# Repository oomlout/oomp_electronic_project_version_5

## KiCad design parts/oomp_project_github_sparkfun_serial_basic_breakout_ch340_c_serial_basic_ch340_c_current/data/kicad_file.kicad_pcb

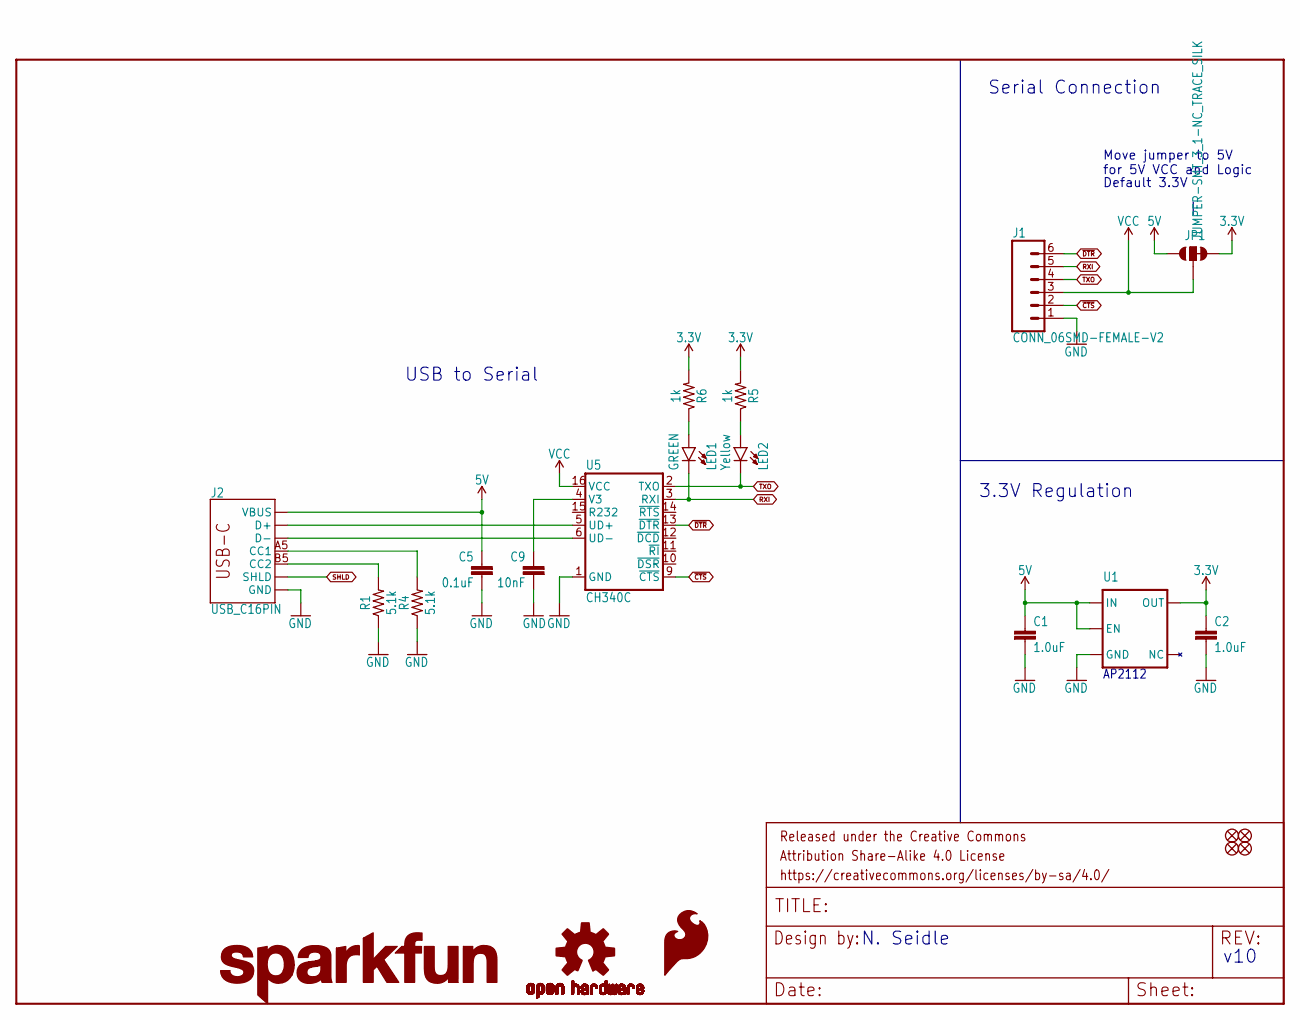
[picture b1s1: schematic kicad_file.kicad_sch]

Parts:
C1, C2: 1.0uF; 0603
C5: 0.1uF; 0603
C9: 10nF; 0603
FRAME1: FRAME-LETTER; CREATIVE_COMMONS
J1: CONN_06SMD-FEMALE-V2; 1X06-SMD-FEMALE
J2: USB_C16PIN; USB-C-16P
JP1: JUMPER-SMT_3_1-NC_TRACE_SILK; SMT-JUMPER_3_1-NC_TRACE_SILK
JP3, JP4, JP5, JP6: FIDUCIAL1X2; FIDUCIAL-1X2
LED1: GREEN; LED-0603
LED2: Yellow; LED-0603
LOGO1: OSHW-LOGOS; OSHW-LOGO-S
LOGO2: SFE_LOGO_FLAME.1_INCH; SFE_LOGO_FLAME_.1
LOGO3: SFE_LOGO_NAME.1_INCH; SFE_LOGO_NAME_.1
R1, R4: 5.1k; 0603
R5, R6: 1k; 0603
U1: 3.3V; SOT23-5
U5: CH340C; SO016

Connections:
3.3V: C2.1, JP1.3, R5.2, R6.2, U1.5 (OUT)
5V: C1.1, C5.1, J2.VBUS1 (VBUS), J2.VBUS2 (VBUS), JP1.1, U1.1 (IN), U1.3 (EN)
CC1: J2.A5 (CC1), R4.2
CC2: J2.B5 (CC2), R1.2
D+: J2.A6 (D+), J2.B6 (D+), U5.5 (UD+)
D-: J2.A7 (D-), J2.B7 (D-), U5.6 (UD-)
GND: C1.2, C2.2, C5.2, C9.2, J1.1, J2.GND, J2.GND2 (GND), R1.1, R4.1, U1.2 (GND), U5.1 (GND)
unnamed: C9.1, U5.4 (V3)
unnamed: LED1.A, R6.1
unnamed: LED2.A, R5.1
RXI: J1.5, LED1.C, U5.3 (RXI)
SHLD: J2.SHLD1 (SHLD), J2.SHLD2 (SHLD), J2.SHLD3 (SHLD), J2.SHLD4 (SHLD), J2.SHLD5 (SHLD), J2.SHLD6 (SHLD), J2.SHLD7 (SHLD), J2.SHLD8 (SHLD)
TXO: J1.4, LED2.C, U5.2 (TXO)
VCC: J1.3, JP1.2, U5.16 (VCC)
~CTS: J1.2, U5.9 (~CTS)
~DTR: J1.6, U5.13 (~DTR)

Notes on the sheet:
3.3V Regulation
v10
Default 3.3V
AP2112
USB to Serial
Serial Connection
N. Seidle
Move jumper to 5V for 5V VCC and Logic

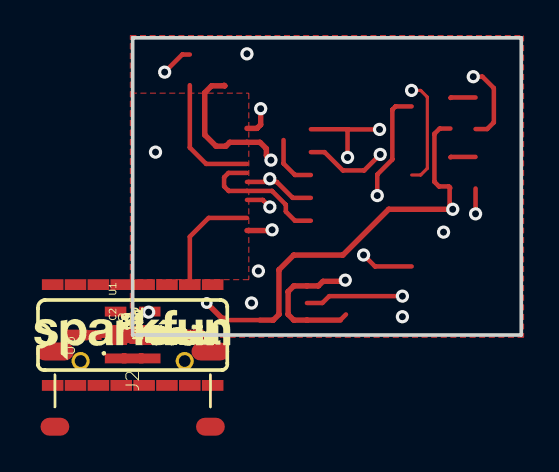
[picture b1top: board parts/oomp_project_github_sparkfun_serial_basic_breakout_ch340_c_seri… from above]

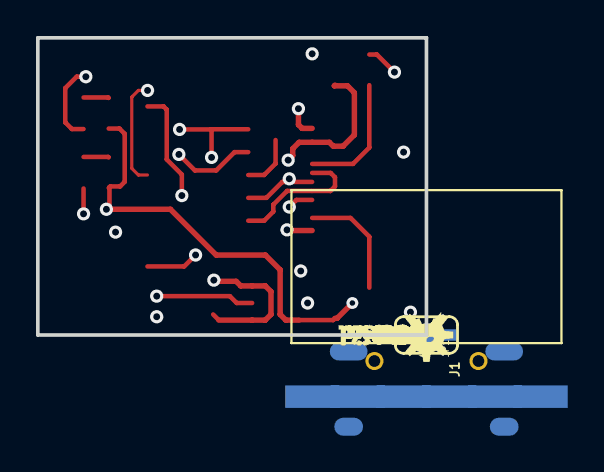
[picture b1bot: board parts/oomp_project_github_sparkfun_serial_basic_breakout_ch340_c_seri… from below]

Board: 4 copper layers, 21.6 x 16.5 mm, 43 parts (16 on the bottom side), 16 nets.

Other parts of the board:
U$1, U$14: CTS1
U$2: 3#3V8
U$3: 5V9
U$4, U$9: SERIAL0
U$5, U$12: TXO0
U$6, U$13: VCC2
U$7, U$11: BASIC1
U$8, U$18: DTR0
U$10, U$21: RXI1
U$15, U$19: GND5
U$17: BLK6
U$20: GRN7

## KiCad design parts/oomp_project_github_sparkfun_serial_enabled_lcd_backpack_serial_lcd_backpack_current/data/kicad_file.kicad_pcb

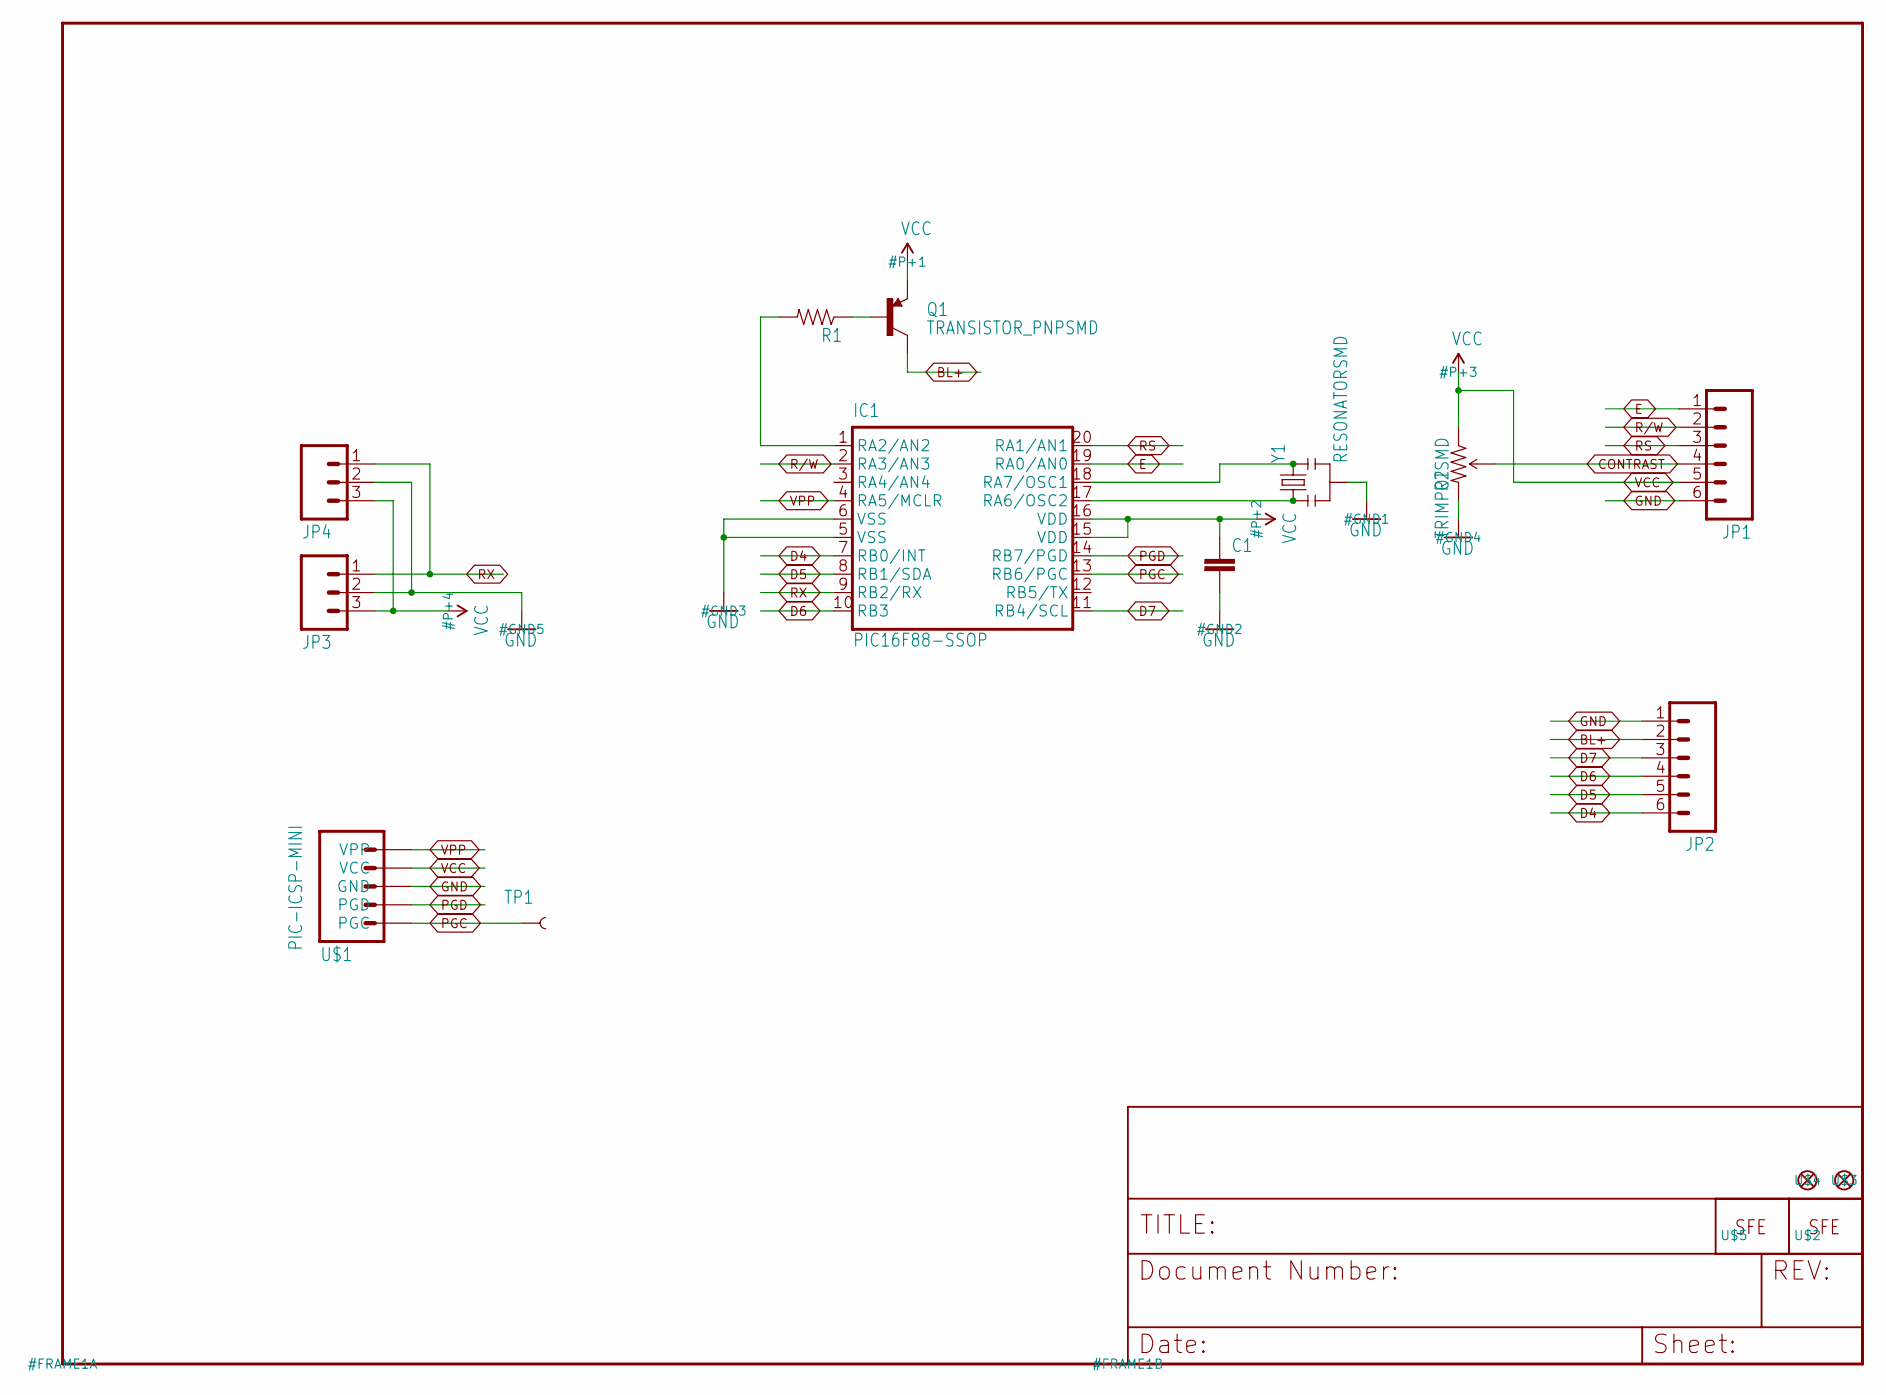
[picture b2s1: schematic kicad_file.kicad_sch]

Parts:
C1: CAP0402-CAP; 0402-CAP
IC1: PIC16F88-SSOP; SSOP20
JP1, JP2: M06LOCK; 1X06_LOCK
JP3: M03PTH; 1X03
JP4: M03SCREW_LOCK; SCREWTERMINAL-3.5MM-3_LOCK.007S
Q1: TRANSISTOR_PNPSMD; SOT23-3
R1: RESISTOR0402-RES; 0402-RES
R2: TRIMPOTSMD; TRIMPOT-3MM
TP1: TEST-POINT3X5; PAD.03X.05
U$1: PIC-ICSP-MINI
U$2: LOGO-FLAME-LARGE
U$3, U$4: FIDUCIAL1X2; FIDUCIAL-1X2
U$5: LOGO-SFENEW; SFE-NEW-WEBLOGO
Y1: RESONATORSMD; RESONATOR-SMD

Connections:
BL+: JP2.2, Q1.3 (C)
CONTRAST: JP1.4, R2.2 (WIPER)
D4: IC1.7 (RB0/INT), JP2.6
D5: IC1.8 (RB1/SDA), JP2.5
D6: IC1.10 (RB3), JP2.4
D7: IC1.11 (RB4/SCL), JP2.3
E: IC1.19 (RA0/AN0), JP1.1
GND: C1.2, IC1.5 (VSS), IC1.6 (VSS), JP1.6, JP2.1, JP3.2, JP4.2, R2.3 (CW), U$1.3 (GND), Y1.2
unnamed: IC1.18 (RA7/OSC1), Y1.3
unnamed: IC1.17 (RA6/OSC2), Y1.1
unnamed: IC1.1 (RA2/AN2), R1.2
unnamed: Q1.1 (B), R1.1
PGC: IC1.13 (RB6/PGC), TP1.P$1, U$1.5 (PGC)
PGD: IC1.14 (RB7/PGD), U$1.4 (PGD)
R/W: IC1.2 (RA3/AN3), JP1.2
RS: IC1.20 (RA1/AN1), JP1.3
RX: IC1.9 (RB2/RX), JP3.1, JP4.1
VCC: C1.1, IC1.15 (VDD), IC1.16 (VDD), JP1.5, JP3.3, JP4.3, Q1.2 (E), R2.1 (CCW), U$1.2 (VCC)
VPP: IC1.4 (RA5/MCLR), U$1.1 (VPP)

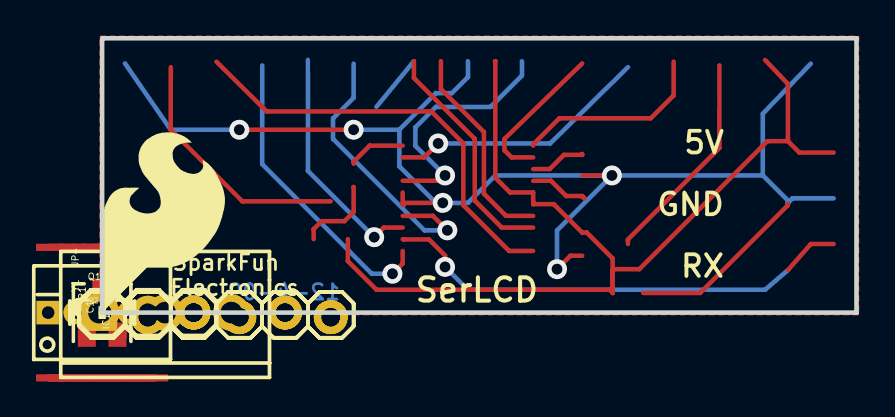
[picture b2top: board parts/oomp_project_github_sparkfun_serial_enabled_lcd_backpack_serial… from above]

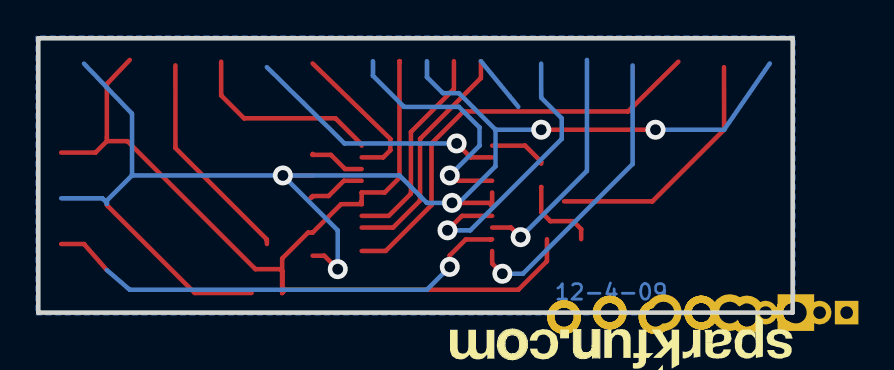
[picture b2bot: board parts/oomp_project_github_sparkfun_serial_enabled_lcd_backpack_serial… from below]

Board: 2 copper layers, 41.9 x 15.2 mm, 16 parts (2 on the bottom side), 19 nets.

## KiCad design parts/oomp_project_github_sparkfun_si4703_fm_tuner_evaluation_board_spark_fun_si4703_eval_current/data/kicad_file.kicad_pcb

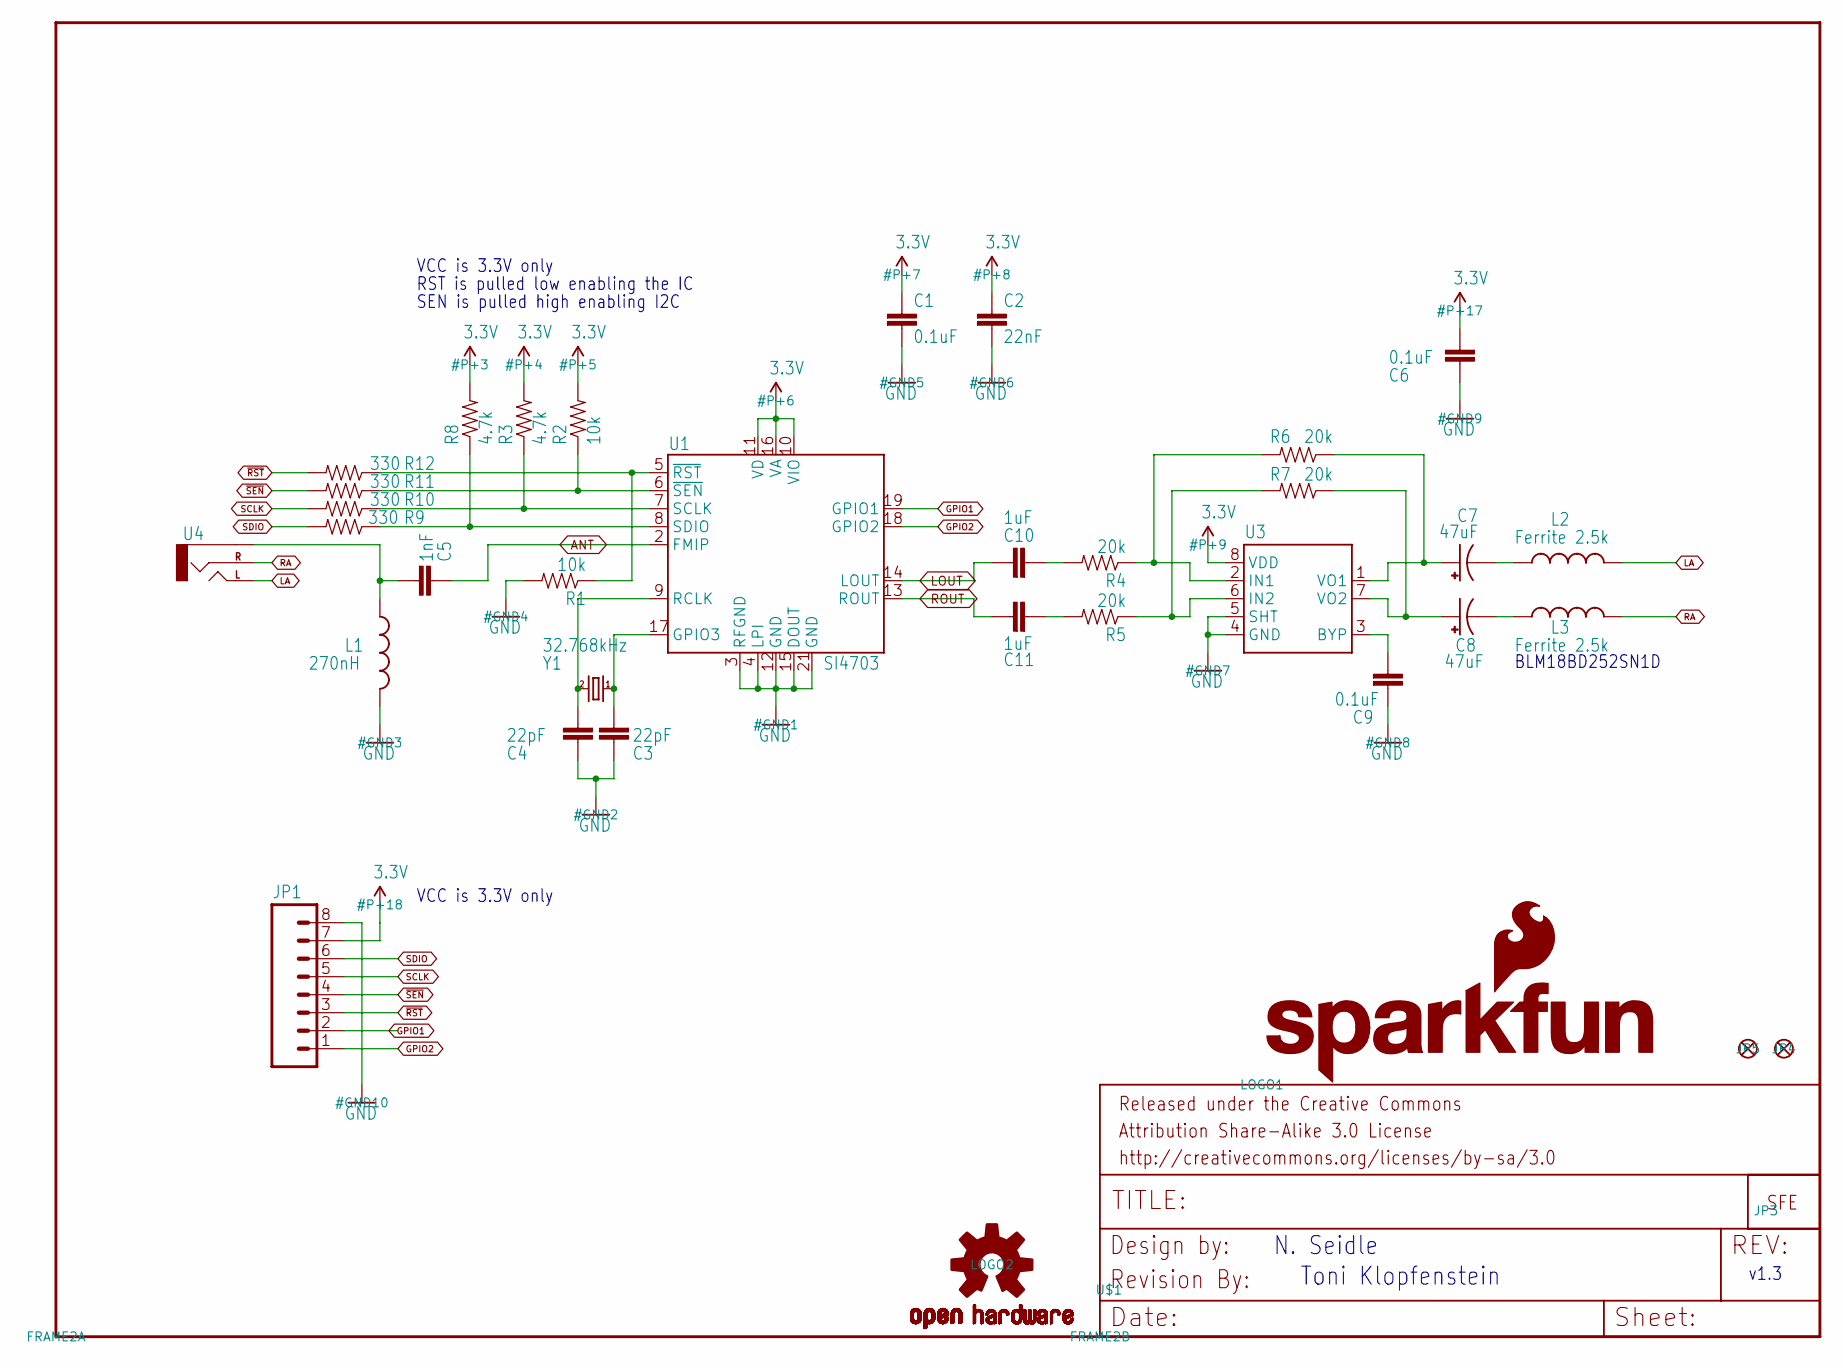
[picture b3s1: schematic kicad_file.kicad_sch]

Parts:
C1, C6, C9: 0.1uF; 0603-CAP
C2: 22nF; 0603-CAP
C3, C4: 22pF; 0603-CAP
C5: 1nF; 0603-CAP
C7, C8: 47uF; EIA3528
C10, C11: 1uF; 0603-CAP
FRAME2: FRAME-LETTER; CREATIVE_COMMONS
JP1: M08; 1X08
JP3: LOGO-SFESK; SFE-LOGO-FLAME
JP4, JP5: FIDUCIAL1X2; FIDUCIAL-1X2
L1: 270nH; 0603
L2, L3: Ferrite 2.5k; 0603
LOGO1: SFE_LOGO_NAME_FLAME.1_INCH; SFE_LOGO_NAME_FLAME_.1
LOGO2: OSHW-LOGOS; OSHW-LOGO-S
R1, R2: 10k; 0603-RES
R3, R8: 4.7k; 0603
R4, R5, R6, R7: 20k; 0603-RES
R9, R10, R11, R12: 330; 0603-RES
U1: SI4703; SI470X
U3: TPA6111; SO08-TIGHT
U4: AUDIO-JACKSMD2; AUDIO-JACK-3.5MM-SMD
U$1: REVISION
Y1: 32.768kHz; CRYSTAL-32KHZ-SMD

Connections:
3.3V: C1.1, C2.1, C6.2, JP1.7, R2.2, R3.2, R8.2, U1.10 (VIO), U1.11 (VD), U1.16 (VA), U3.8 (VDD)
ANT: C5.1, U1.2 (FMIP)
GND: C1.2, C2.2, C3.1, C4.1, C6.1, C9.2, JP1.8, L1.2, R1.2, U1.3 (RFGND), U1.4 (LPI), U1.12 (GND), U1.15 (DOUT), U1.21 (GND), U3.4 (GND), U3.5 (SHT)
GPIO1: JP1.2, U1.19 (GPIO1)
GPIO2: JP1.1, U1.18 (GPIO2)
LA: L2.2, U4.TIP (LEFT)
LOUT: C10.1, U1.14 (LOUT)
unnamed: C4.2, U1.9 (RCLK), Y1.X2 (2)
unnamed: C3.2, U1.17 (GPIO3), Y1.X1 (1)
unnamed: C5.2, L1.1, U4.SLEEVE
unnamed: C7.C (-), L2.1
unnamed: C7.A (+), R6.1, U3.1 (VO1)
unnamed: C8.A (+), R7.1, U3.7 (VO2)
unnamed: C8.C (-), L3.1
unnamed: C9.1, U3.3 (BYP)
unnamed: R4.1, R6.2, U3.2 (IN1)
unnamed: R5.1, R7.2, U3.6 (IN2)
unnamed: C10.2, R4.2
unnamed: C11.2, R5.2
RA: L3.2, U4.RING (RIGHT)
ROUT: C11.1, U1.13 (ROUT)
SCLK: JP1.5, R10.2
SCLK-L: R3.1, R10.1, U1.7 (SCLK)
SDIO: JP1.6, R9.2
SDIO-L: R8.1, R9.1, U1.8 (SDIO)
~RST-L: R1.1, R12.1, U1.5 (~RST)
~RST: JP1.3, R12.2
~SEN-L: R2.1, R11.1, U1.6 (~SEN)
~SEN: JP1.4, R11.2

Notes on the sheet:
VCC is 3.3V only~{}
N. Seidle
Toni Klopfenstein
SEN is pulled high enabling I2C
v1.3
BLM18BD252SN1D
RST is pulled low enabling the IC

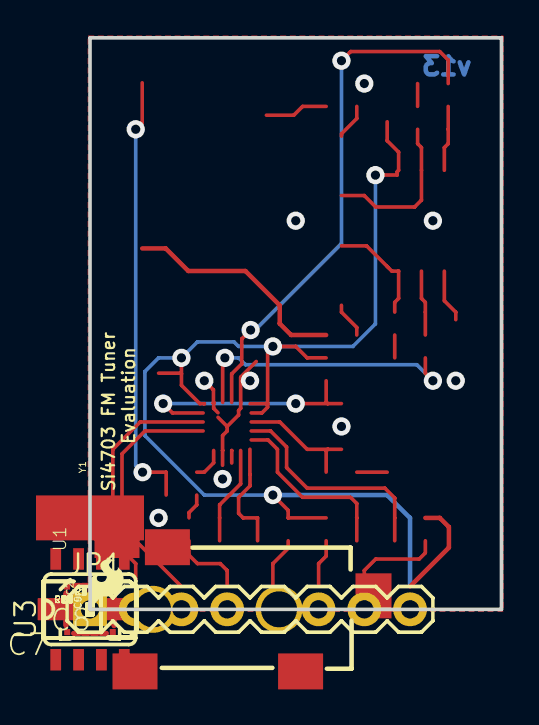
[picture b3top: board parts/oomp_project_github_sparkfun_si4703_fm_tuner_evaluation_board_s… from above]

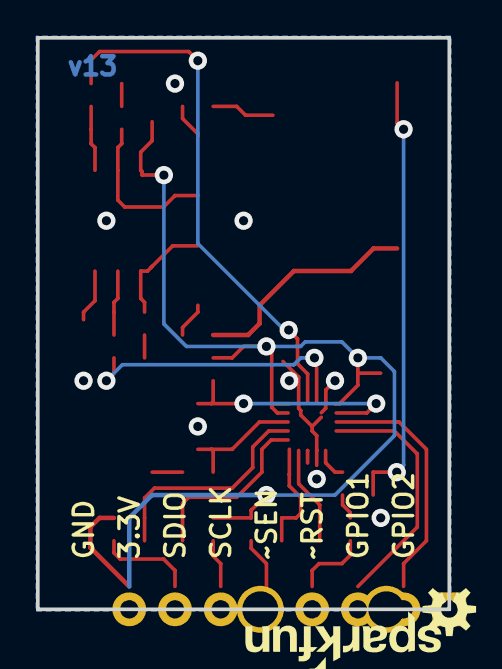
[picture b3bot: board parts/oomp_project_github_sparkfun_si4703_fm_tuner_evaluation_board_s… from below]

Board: 2 copper layers, 22.9 x 31.8 mm, 38 parts (2 on the bottom side), 29 nets.

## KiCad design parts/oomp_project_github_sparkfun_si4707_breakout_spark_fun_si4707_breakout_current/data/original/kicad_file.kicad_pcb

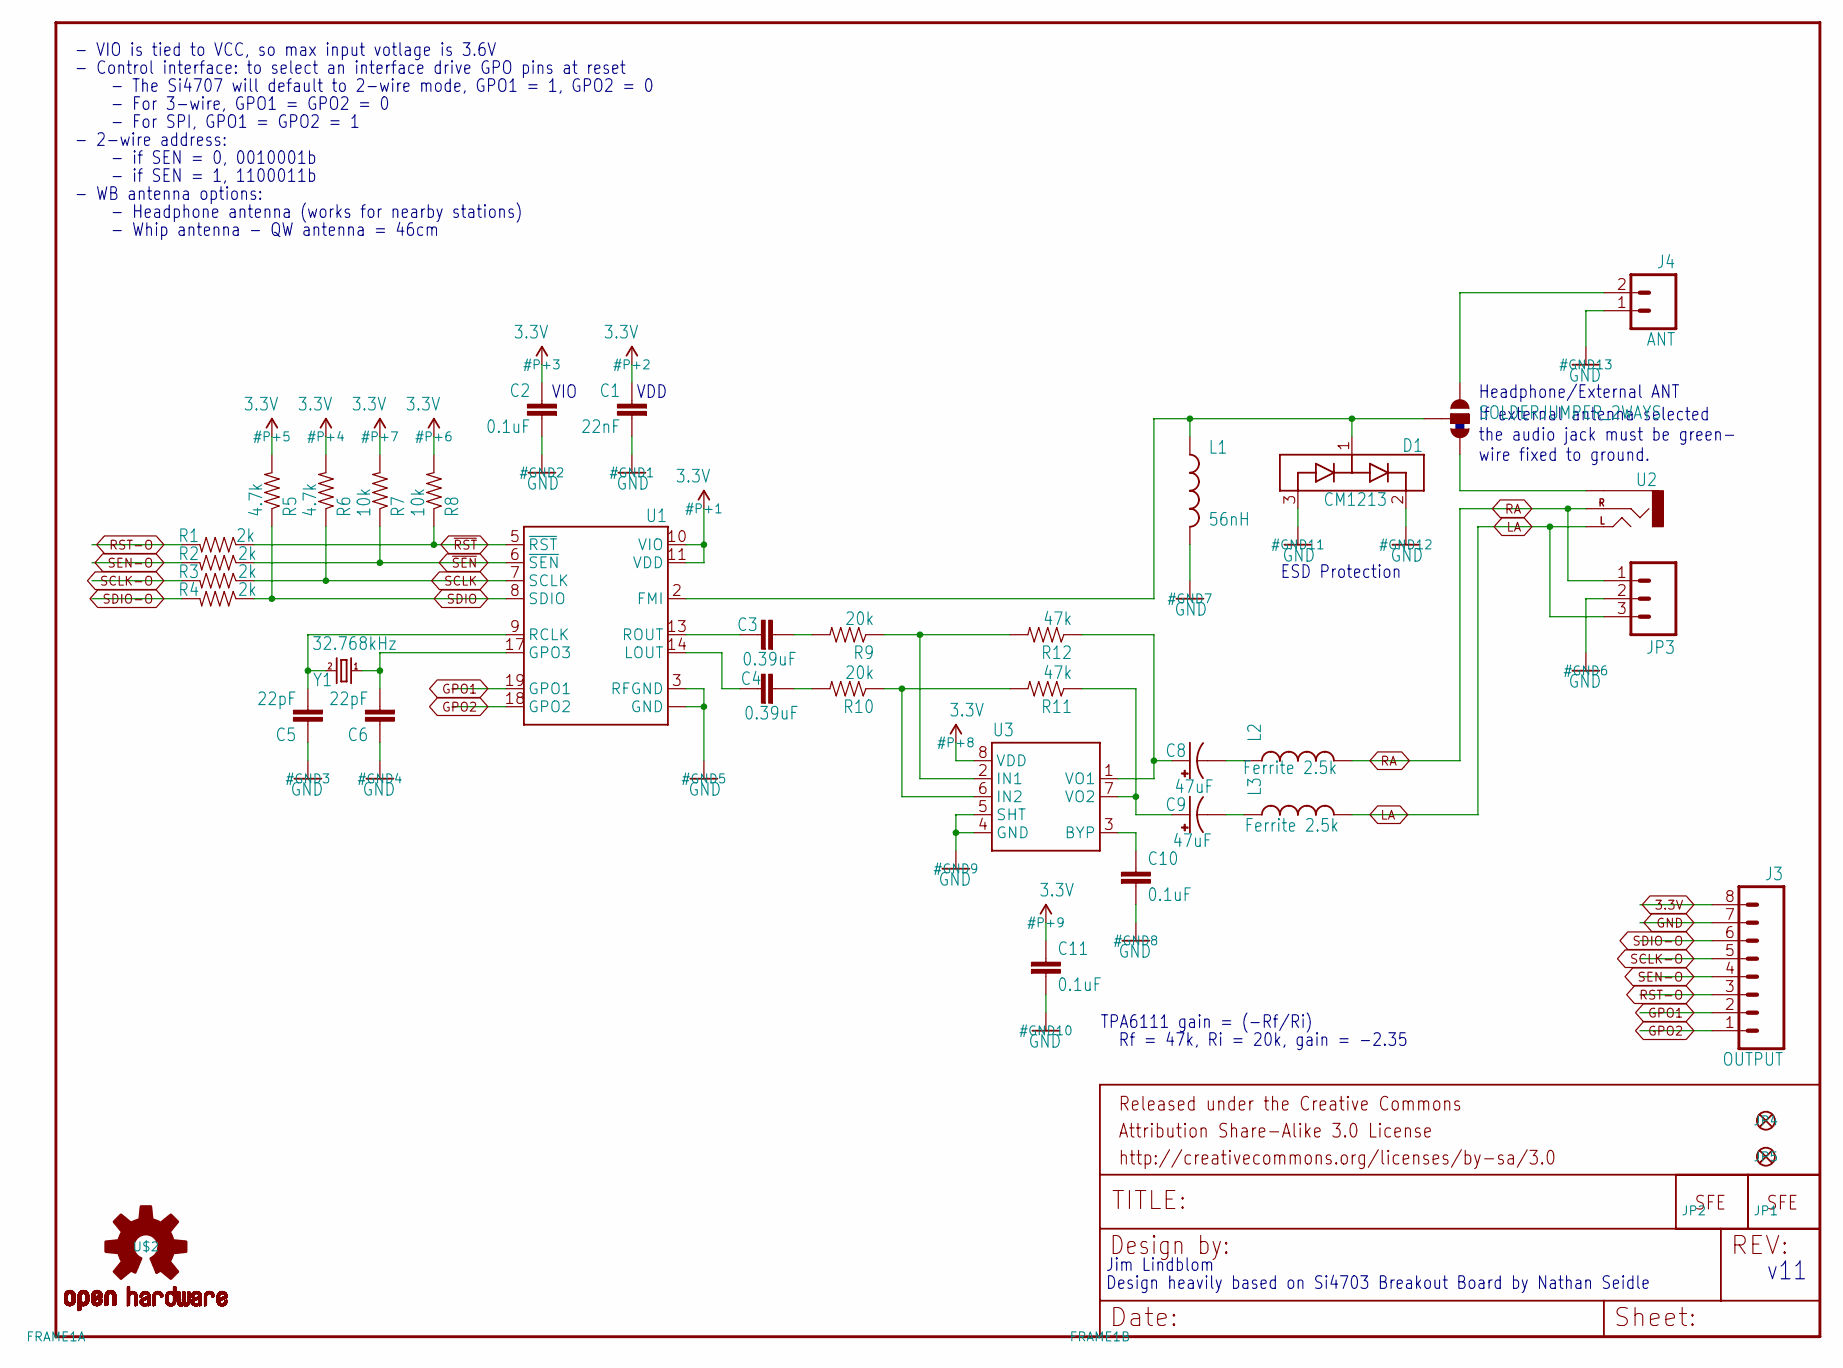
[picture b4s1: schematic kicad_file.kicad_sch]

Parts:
C1: 22nF; 0402-CAP
C2, C10, C11: 0.1uF; 0402-CAP
C3, C4: 0.39uF; 0402-CAP
C5, C6: 22pF; 0402-CAP
C8, C9: 47uF; EIA3528
D1: CM1213; SOT23-3
FRAME1: FRAME-LETTER; CREATIVE_COMMONS
J3: OUTPUT; 1X08
J4: ANT; 1X02
JP1: LOGO-SFENEW; SFE-NEW-WEBLOGO
JP2: LOGO-SFESK; SFE-LOGO-FLAME
JP3: M03PTH; 1X03
JP4, JP5: FIDUCIALUFIDUCIAL; MICRO-FIDUCIAL
L1: 56nH; 0603
L2, L3: Ferrite 2.5k; C0402
R1, R2, R3, R4: 2k; 0402-RES
R5, R6: 4.7k; 0402-RES
R7, R8: 10k; 0402-RES
R9, R10: 20k; 0402-RES
R11, R12: 47k; 0402-RES
SJ2: SOLDERJUMPER_2WAYS; SJ_3
U1: SI4707; SI470X
U2: AUDIO-JACKSMD2; AUDIO-JACK-3.5MM-SMD
U3: TPA6111; SPARKFUN_SO08
U$2: OSHW-LOGOS; OSHW-LOGO-S
Y1: 32.768kHz; CRYSTAL-32KHZ-SMD

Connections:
3.3V: C1.1, C2.1, C11.1, J3.8, R5.2, R6.2, R7.2, R8.2, U1.10 (VIO), U1.11 (VDD), U3.8 (VDD)
GND: C1.2, C2.2, C5.1, C6.1, C10.2, C11.2, D1.2 (VP), D1.3 (VN), J3.7, J4.1, JP3.2, L1.2, U1.3 (RFGND), U1.4 (GND), U1.12 (GND), U1.15 (GND), U1.16 (GND), U1.21 (GND), U3.4 (GND), U3.5 (SHT)
GPO1: J3.2, U1.19 (GPO1)
GPO2: J3.1, U1.18 (GPO2)
J1: D1.1 (CH1), L1.1, SJ2.2, U1.2 (FMI)
LA: JP3.3, L3.2, U2.TIP (LEFT)
LOUT: C4.1, U1.14 (LOUT)
unnamed: C3.2, R9.2
unnamed: C4.2, R10.2
unnamed: C6.2, U1.17 (GPO3), Y1.X1 (1)
unnamed: SJ2.1, U2.SLEEVE
unnamed: J4.2, SJ2.3
unnamed: R9.1, R12.2, U3.2 (IN1)
unnamed: R10.1, R11.2, U3.6 (IN2)
unnamed: C10.1, U3.3 (BYP)
unnamed: C8.C (-), L2.1
unnamed: C9.C (-), L3.1
unnamed: C8.A (+), R12.1, U3.1 (VO1)
unnamed: C9.A (+), R11.1, U3.7 (VO2)
RA: JP3.1, L2.2, U2.RING (RIGHT)
RCLK: C5.2, U1.9 (RCLK), Y1.X2 (2)
ROUT: C3.1, U1.13 (ROUT)
RST-O: J3.3, R1.2
SCLK: R3.1, R6.1, U1.7 (SCLK)
SCLK-O: J3.5, R3.2
SDIO: R4.1, R5.1, U1.8 (SDIO)
SDIO-O: J3.6, R4.2
SEN-O: J3.4, R2.2
~RST: R1.1, R8.1, U1.5 (~RST)
~SEN: R2.1, R7.1, U1.6 (~SEN)

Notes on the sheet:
TPA6111 gain = (-Rf/Ri)
- Control interface: to select an interface drive GPO pins at reset
- Whip antenna - QW antenna =~{} 46cm
VIO
- Headphone antenna (works for nearby stations)
Headphone/External ANT
- VIO is tied to VCC, so max input votlage is 3.6V
- The Si4707 will default to 2-wire mode, GPO1 = 1, GPO2 = 0
Design heavily based on Si4703 Breakout Board by Nathan Seidle
- if SEN = 0, 0010001b
Rf = 47k, Ri = 20k, gain = -2.35
v11
VDD
If external antenna selected the audio jack must be green- wire fixed to ground.
- For SPI, GPO1 = GPO2 = 1
Jim Lindblom
- WB antenna options:
ESD Protection
- if SEN = 1, 1100011b
- 2-wire address:
- For 3-wire, GPO1 = GPO2 = 0

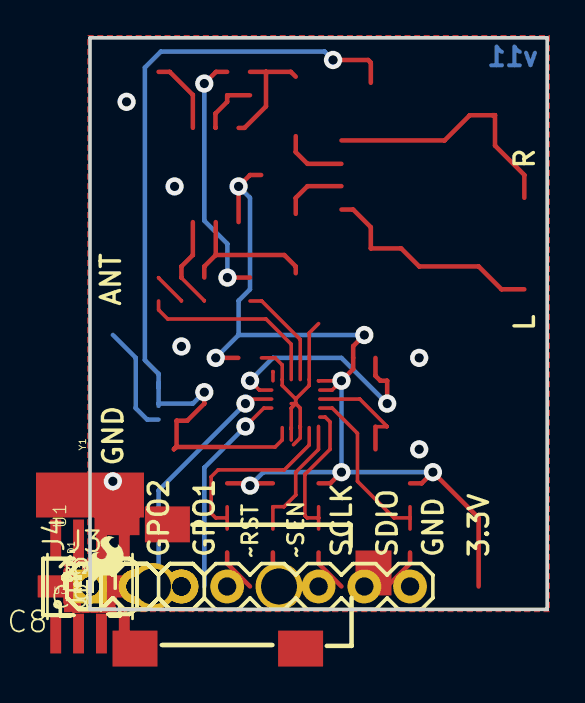
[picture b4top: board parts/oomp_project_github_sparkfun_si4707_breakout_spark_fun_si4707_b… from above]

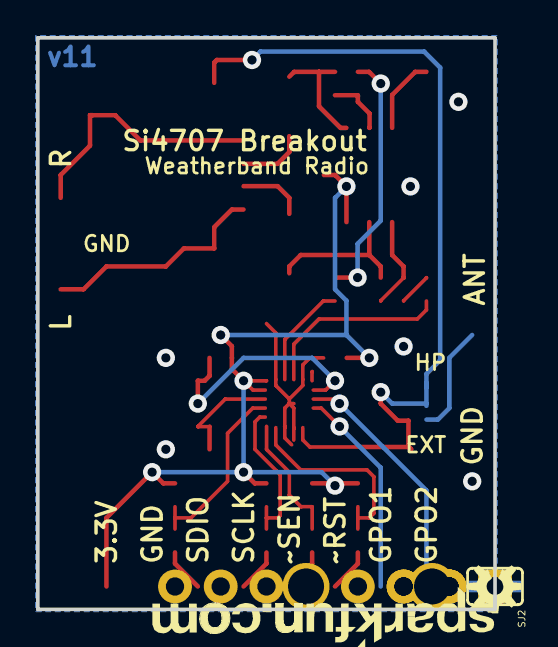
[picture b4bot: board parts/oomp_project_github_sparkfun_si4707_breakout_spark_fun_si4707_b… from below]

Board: 2 copper layers, 25.4 x 31.8 mm, 40 parts (3 on the bottom side), 30 nets.

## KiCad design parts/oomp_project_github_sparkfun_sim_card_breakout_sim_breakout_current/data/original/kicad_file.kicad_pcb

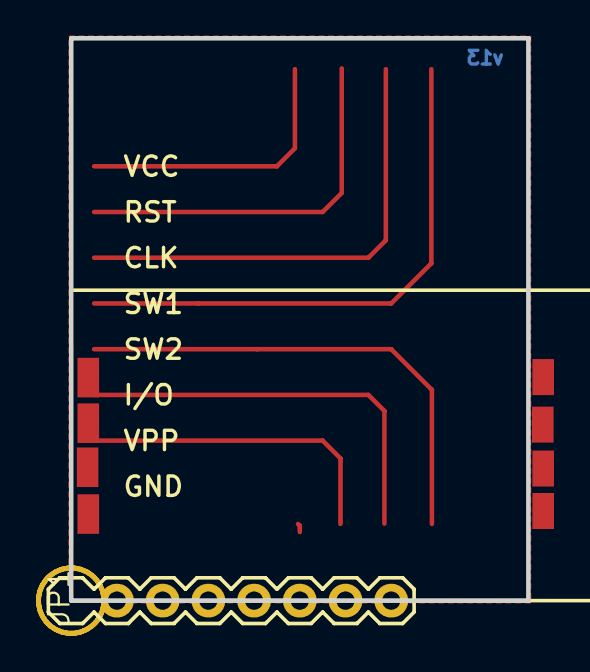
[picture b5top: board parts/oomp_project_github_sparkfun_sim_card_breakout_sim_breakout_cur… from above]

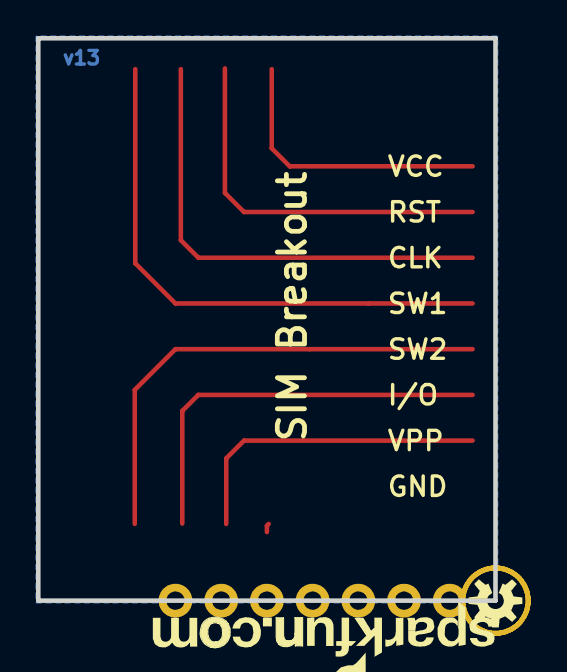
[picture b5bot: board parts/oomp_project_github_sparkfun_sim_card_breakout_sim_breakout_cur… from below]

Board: 2 copper layers, 25.4 x 31.2 mm, 9 parts (2 on the bottom side), 8 nets.

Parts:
FID1, FID2: FIDUCIALUFIDUCIAL; MICRO-FIDUCIAL
FRAME2: FRAME-LETTER; CREATIVE_COMMONS
JP1: 1X08
LOGO1: OSHW-LOGOS; OSHW-LOGO-S
STANDOFF1, STANDOFF2: STAND-OFF
U2: SIMHOLDER; SIMHOLDER2
U$1: SFE-NEW-WEBLOGO

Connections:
CLK: JP1.3, U2.3
GND: JP1.8, U2.8
I/O: JP1.6, U2.6
RST: JP1.2, U2.2
SW1: JP1.4, U2.4
SW2: JP1.5, U2.5
VCC: JP1.1, U2.1
VPP: JP1.7, U2.7

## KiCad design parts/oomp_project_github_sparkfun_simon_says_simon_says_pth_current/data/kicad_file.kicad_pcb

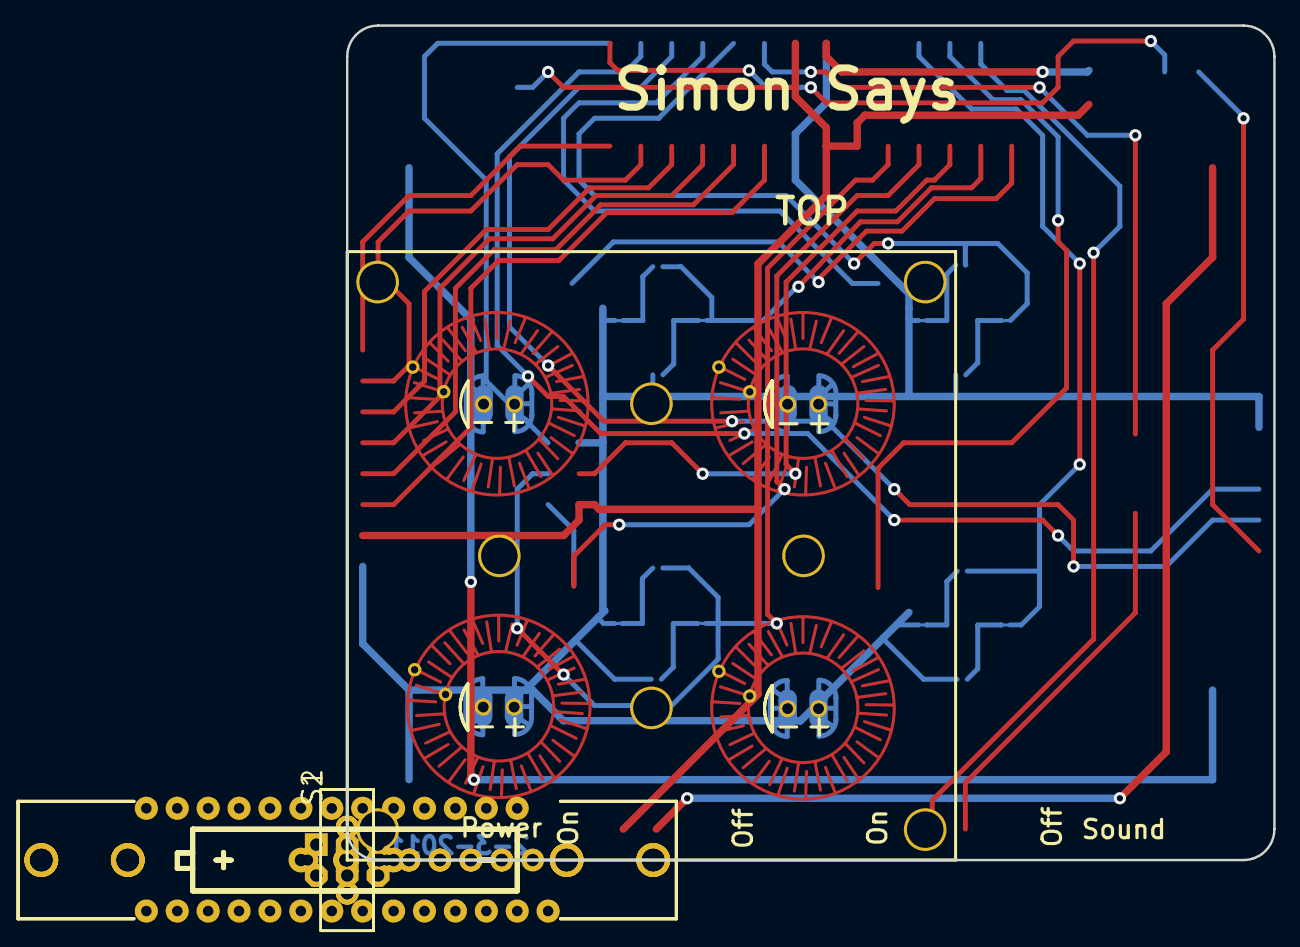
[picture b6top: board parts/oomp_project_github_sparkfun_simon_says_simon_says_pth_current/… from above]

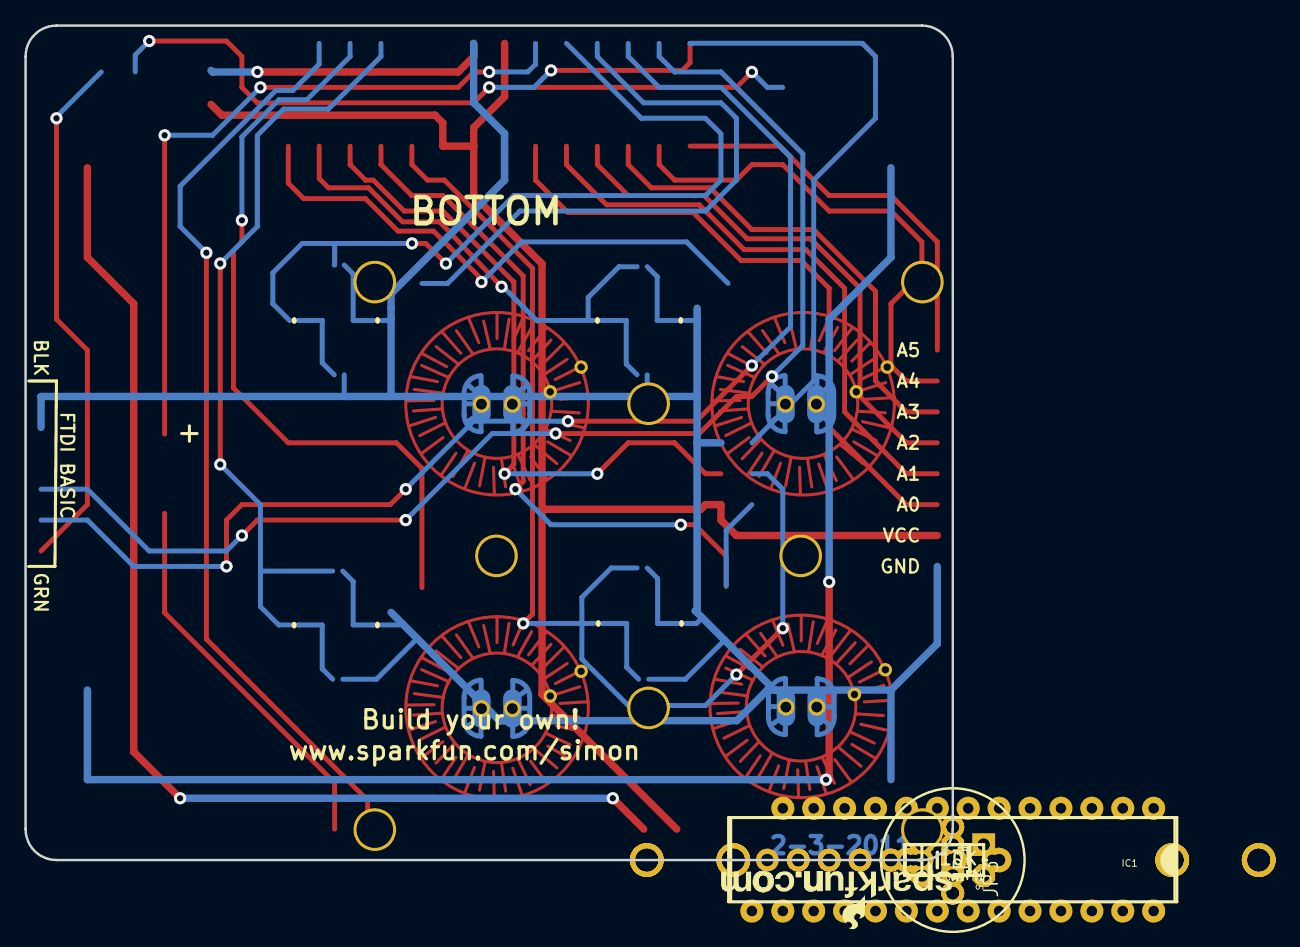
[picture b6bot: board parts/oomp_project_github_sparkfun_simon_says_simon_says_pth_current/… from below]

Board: 2 copper layers, 76.2 x 68.6 mm, 23 parts (17 on the bottom side), 26 nets.

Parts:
BAT1, BAT2: AA; BATTERY-AA-KIT
C1, C2: 0.1uF; CAP-PTH-SMALL-KIT
IC1: AVR-MEGA8-P; DIL28-3-SIMON-KIT
JP1: Serial; 1X06-NOSILK
JP2, JP5, JP6, JP7, JP8, JP9, JP10, JP11: SJ_2S_NO_SILK
JP3: AVR_SPI_PRG_6NS; 2X3-NS
JP4: 1X08NOSILK
P1-0: BUTTONPAD-2X2SINGLEKIT; BUTTONPAD-2X2SINGLE-KIT
R1: 10K; AXIAL-0.3-KIT
S1: Power; SWITCH-SPDT_KIT
S2: SWITCH-SPDT_KIT
SG1: BUZZER; BUZZER-12MM-KIT
U$1: LOGO-SFENEW; SFE-NEW-WEBLOGO
U$2: CREATIVE_COMMONS

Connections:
3.3V: C1.2, IC1.7, IC1.20, IC1.21, JP3.2, JP4.2, R1.P$2, S1.3
A0: IC1.23, JP4.3
A1: IC1.24, JP4.4
A2: IC1.25, JP4.5
A3: IC1.26, JP4.6
A4: IC1.27, JP4.7
A5: IC1.28, JP4.8
BUTTON_BLUE: IC1.18, JP3.1, P1-0.SIG1
BUTTON_GREEN: IC1.4, P1-0.SIG7
BUTTON_RED: IC1.15, P1-0.SIG5
BUTTON_YELLOW: IC1.12, P1-0.SIG3
BUZZER1: IC1.6, SG1.+
BUZZER2: IC1.13, S2.3
DTR: C2.1, JP1.1
GND: BAT1.GND@1, C1.1, IC1.8, IC1.22, JP1.5, JP1.6, JP2.1, JP3.6, JP4.1, JP5.2, JP6.2, JP7.1, JP8.2, JP9.1, JP10.2, JP11.1, P1-0.K1, P1-0.K2, P1-0.K3, P1-0.K4, P1-0.SIG2, P1-0.SIG4, P1-0.SIG6, P1-0.SIG8
LED_BLUE/SCK: IC1.19, JP3.3, JP8.1, JP9.2, P1-0.A1
LED_GREEN: IC1.5, JP6.1, JP7.2, P1-0.A4
LED_RED: IC1.16, JP2.2, JP5.1, P1-0.A3
LED_YELLOW: IC1.11, JP10.1, JP11.2, P1-0.A2
MOSI: IC1.17, JP3.4
unnamed: BAT2.PWR@1, S1.2
unnamed: S2.2, SG1.-
unnamed: BAT1.PWR@1, BAT2.GND@1
RESET: C2.2, IC1.1, JP3.5, R1.P$1
RX-I: IC1.2, JP1.3
TX-O: IC1.3, JP1.2

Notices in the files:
parts/oomp_project_github_sparkfun_serial_basic_breakout_ch340_c_serial_basic_ch340_c_current/data/kicad_file.kicad_sch:
Released under the Creative Commons
https://creativecommons.org/licenses/by-sa/4.0
parts/oomp_project_github_sparkfun_si4703_fm_tuner_evaluation_board_spark_fun_si4703_eval_current/data/original/kicad_file.kicad_sch:
http://creativecommons.org/licenses/by-sa/3.0
parts/oomp_project_github_sparkfun_simon_says_simon_says_pth_current/data/original/kicad_file.kicad_sch:
Released under the Creative Commons Attribution Share-Alike 3.0 License
